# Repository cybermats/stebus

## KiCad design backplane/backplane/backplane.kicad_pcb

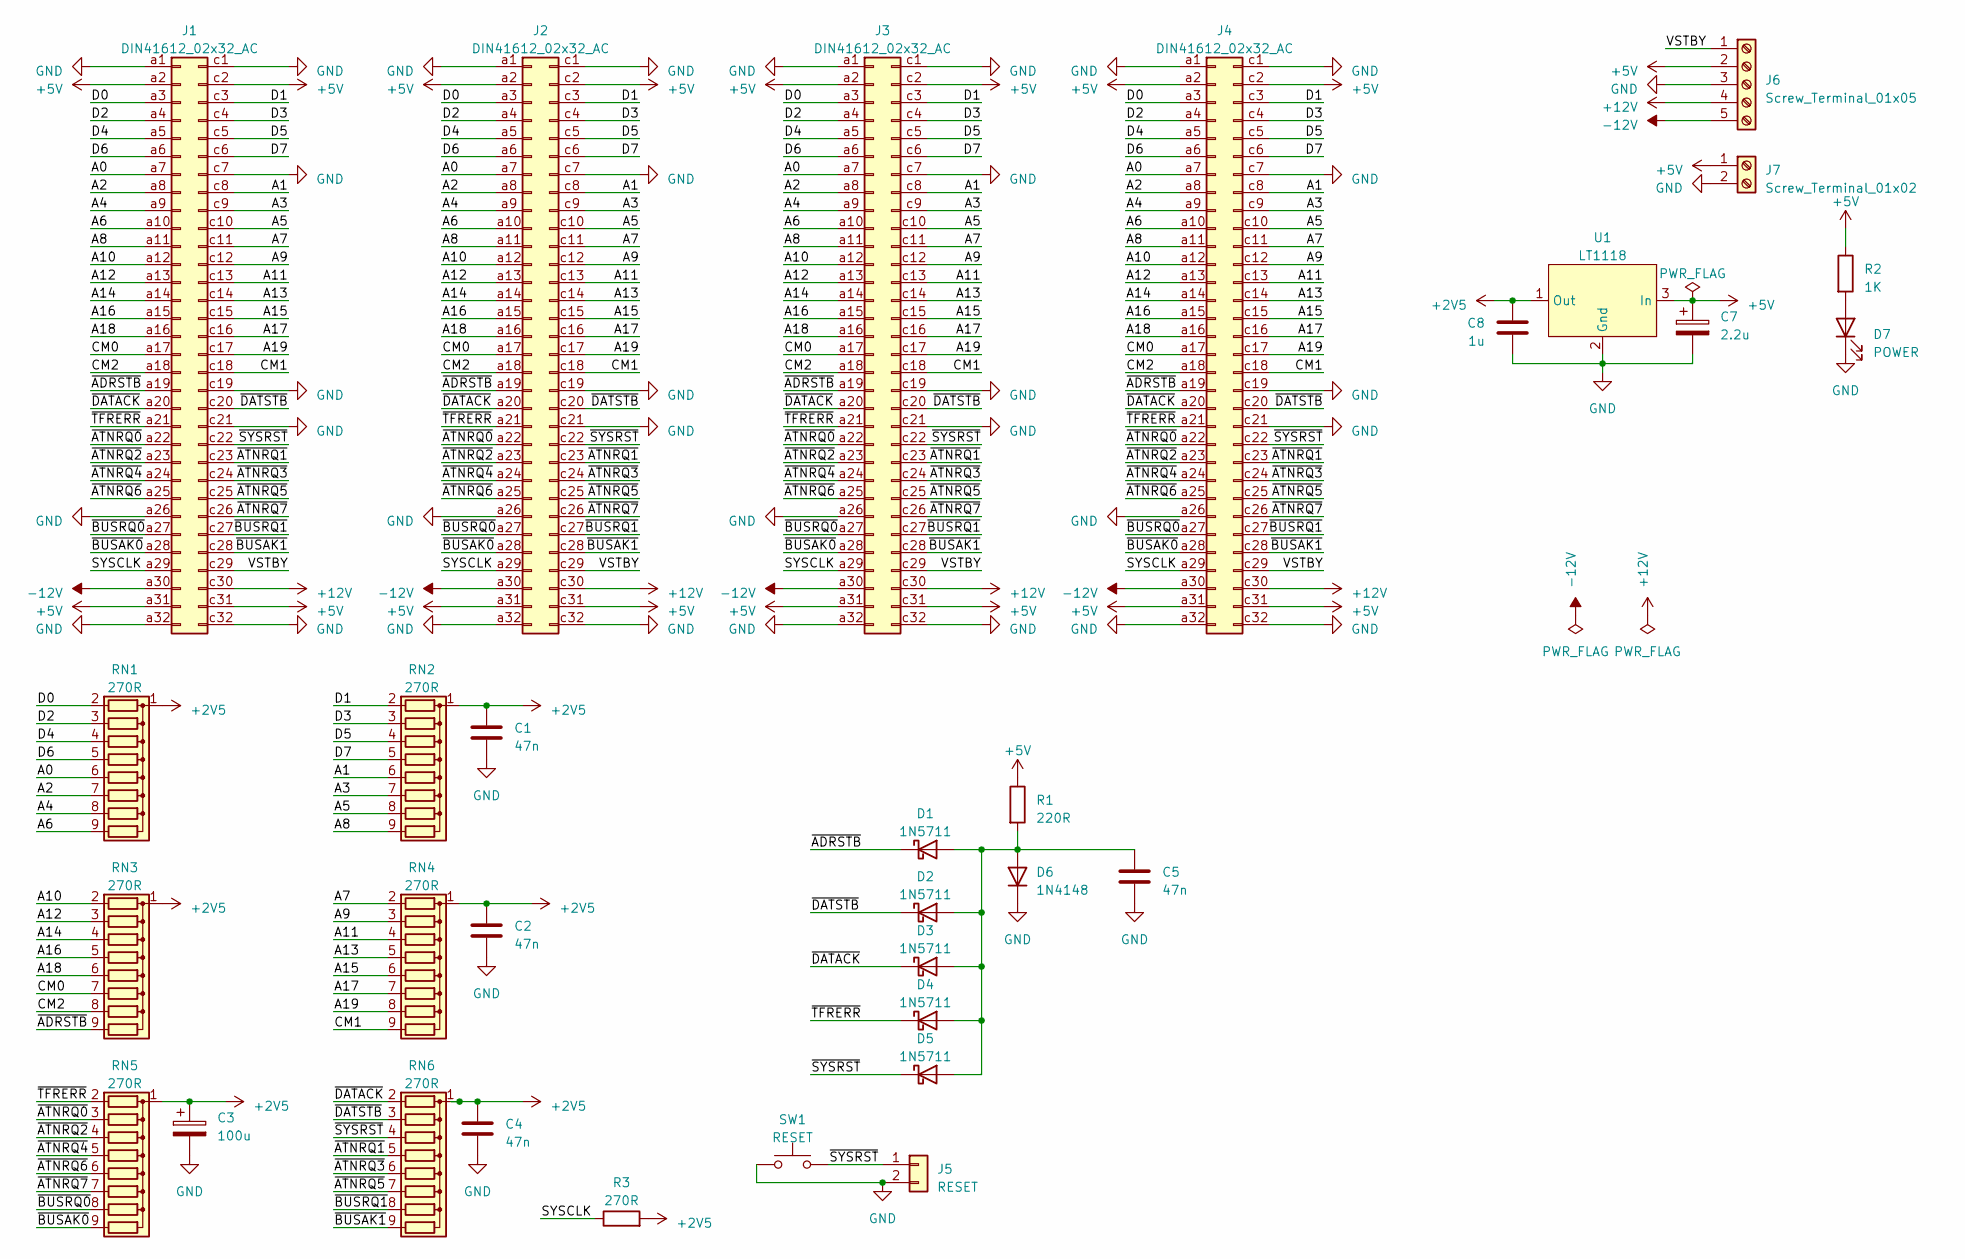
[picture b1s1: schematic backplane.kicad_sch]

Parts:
C1, C2, C4, C5: 47n; C_Disc_D6.0mm_W2.5mm_P5.00mm
C3: 100u; CP_Radial_D5.0mm_P2.00mm
C7: 2.2u; CP_Radial_D5.0mm_P2.00mm
C8: 1u; C_Disc_D6.0mm_W2.5mm_P5.00mm
D1, D2, D3, D4, D5: 1N5711; D_DO-35_SOD27_P7.62mm_Horizontal
D6: 1N4148; D_DO-35_SOD27_P7.62mm_Horizontal
D7: POWER; LED_D3.0mm_Clear
J1, J2, J3, J4: DIN41612_02x32_AC; DIN41612_C_2x32_Female_Vertical_THT
J5: RESET; PinHeader_1x02_P2.54mm_Vertical
J6: Screw_Terminal_01x05; PinHeader_1x05_P2.54mm_Vertical
J7: Screw_Terminal_01x02; TerminalBlock_Phoenix_MPT-0,5-2-2.54_1x02_P2.54mm_Horizontal
R1: 220R; R_Axial_DIN0207_L6.3mm_D2.5mm_P7.62mm_Horizontal
R2: 1K; R_Axial_DIN0207_L6.3mm_D2.5mm_P7.62mm_Horizontal
R3: 270R; R_Axial_DIN0207_L6.3mm_D2.5mm_P7.62mm_Horizontal
RN1, RN2, RN3, RN4, RN5, RN6: 270R; R_Array_SIP9
SW1: RESET; SW_PUSH_6mm
U1: LT1118; SOT-223-3_TabPin2

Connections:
+2V5: C1.1, C2.1, C3.1, C4.1, C8.1, R3.2, RN1.1 (common), RN2.1 (common), RN3.1 (common), RN4.1 (common), RN5.1 (common), RN6.1 (common), U1.1 (Out)
+5V: C7.1, J1.a2, J1.a31, J1.c2, J1.c31, J2.a2, J2.a31, J2.c2, J2.c31, J3.a2, J3.a31, J3.c2, J3.c31, J4.a2, J4.a31, J4.c2, J4.c31, J6.2, J7.1, R1.1, R2.1, U1.3 (In)
+12V: J1.c30, J2.c30, J3.c30, J4.c30, J6.4
-12V: J1.a30, J2.a30, J3.a30, J4.a30, J6.5
/A0: J1.a7, J2.a7, J3.a7, J4.a7, RN1.6 (R5)
/A1: J1.c8, J2.c8, J3.c8, J4.c8, RN2.6 (R5)
/A2: J1.a8, J2.a8, J3.a8, J4.a8, RN1.7 (R6)
/A3: J1.c9, J2.c9, J3.c9, J4.c9, RN2.7 (R6)
/A4: J1.a9, J2.a9, J3.a9, J4.a9, RN1.8 (R7)
/A5: J1.c10, J2.c10, J3.c10, J4.c10, RN2.8 (R7)
/A6: J1.a10, J2.a10, J3.a10, J4.a10, RN1.9 (R8)
/A7: J1.c11, J2.c11, J3.c11, J4.c11, RN4.2 (R1)
/A8: J1.a11, J2.a11, J3.a11, J4.a11, RN2.9 (R8)
/A9: J1.c12, J2.c12, J3.c12, J4.c12, RN4.3 (R2)
/A10: J1.a12, J2.a12, J3.a12, J4.a12, RN3.2 (R1)
/A11: J1.c13, J2.c13, J3.c13, J4.c13, RN4.4 (R3)
/A12: J1.a13, J2.a13, J3.a13, J4.a13, RN3.3 (R2)
/A13: J1.c14, J2.c14, J3.c14, J4.c14, RN4.5 (R4)
/A14: J1.a14, J2.a14, J3.a14, J4.a14, RN3.4 (R3)
/A15: J1.c15, J2.c15, J3.c15, J4.c15, RN4.6 (R5)
/A16: J1.a15, J2.a15, J3.a15, J4.a15, RN3.5 (R4)
/A17: J1.c16, J2.c16, J3.c16, J4.c16, RN4.7 (R6)
/A18: J1.a16, J2.a16, J3.a16, J4.a16, RN3.6 (R5)
/A19: J1.c17, J2.c17, J3.c17, J4.c17, RN4.8 (R7)
/CM0: J1.a17, J2.a17, J3.a17, J4.a17, RN3.7 (R6)
/CM1: J1.c18, J2.c18, J3.c18, J4.c18, RN4.9 (R8)
/CM2: J1.a18, J2.a18, J3.a18, J4.a18, RN3.8 (R7)
/D0: J1.a3, J2.a3, J3.a3, J4.a3, RN1.2 (R1)
/D1: J1.c3, J2.c3, J3.c3, J4.c3, RN2.2 (R1)
/D2: J1.a4, J2.a4, J3.a4, J4.a4, RN1.3 (R2)
/D3: J1.c4, J2.c4, J3.c4, J4.c4, RN2.3 (R2)
/D4: J1.a5, J2.a5, J3.a5, J4.a5, RN1.4 (R3)
/D5: J1.c5, J2.c5, J3.c5, J4.c5, RN2.4 (R3)
/D6: J1.a6, J2.a6, J3.a6, J4.a6, RN1.5 (R4)
/D7: J1.c6, J2.c6, J3.c6, J4.c6, RN2.5 (R4)
/SYSCLK: J1.a29, J2.a29, J3.a29, J4.a29, R3.1
/VSTBY: J1.c29, J2.c29, J3.c29, J4.c29, J6.1
/~ADRSTB: D1.1 (K), J1.a19, J2.a19, J3.a19, J4.a19, RN3.9 (R8)
/~ATNRQ0: J1.a22, J2.a22, J3.a22, J4.a22, RN5.3 (R2)
/~ATNRQ1: J1.c23, J2.c23, J3.c23, J4.c23, RN6.5 (R4)
/~ATNRQ2: J1.a23, J2.a23, J3.a23, J4.a23, RN5.4 (R3)
/~ATNRQ3: J1.c24, J2.c24, J3.c24, J4.c24, RN6.6 (R5)
/~ATNRQ4: J1.a24, J2.a24, J3.a24, J4.a24, RN5.5 (R4)
/~ATNRQ5: J1.c25, J2.c25, J3.c25, J4.c25, RN6.7 (R6)
/~ATNRQ6: J1.a25, J2.a25, J3.a25, J4.a25, RN5.6 (R5)
/~ATNRQ7: J1.c26, J2.c26, J3.c26, J4.c26, RN5.7 (R6)
/~BUSAK0: J1.a28, J2.a28, J3.a28, J4.a28, RN5.9 (R8)
/~BUSAK1: J1.c28, J2.c28, J3.c28, J4.c28, RN6.9 (R8)
/~BUSRQ0: J1.a27, J2.a27, J3.a27, J4.a27, RN5.8 (R7)
/~BUSRQ1: J1.c27, J2.c27, J3.c27, J4.c27, RN6.8 (R7)
/~DATACK: D3.1 (K), J1.a20, J2.a20, J3.a20, J4.a20, RN6.2 (R1)
/~DATSTB: D2.1 (K), J1.c20, J2.c20, J3.c20, J4.c20, RN6.3 (R2)
/~SYSRST: D5.1 (K), J1.c22, J2.c22, J3.c22, J4.c22, J5.1, RN6.4 (R3), SW1.2
/~TFRERR: D4.1 (K), J1.a21, J2.a21, J3.a21, J4.a21, RN5.2 (R1)
GND: C1.2, C2.2, C3.2, C4.2, C5.2, C7.2, C8.2, D6.1 (K), D7.1 (K), J1.a1, J1.a26, J1.a32, J1.c1, J1.c7, J1.c19, J1.c21, J1.c32, J2.a1, J2.a26, J2.a32, J2.c1, J2.c7, J2.c19, J2.c21, J2.c32, J3.a1, J3.a26, J3.a32, J3.c1, J3.c7, J3.c19, J3.c21, J3.c32, J4.a1, J4.a26, J4.a32, J4.c1, J4.c7, J4.c19, J4.c21, J4.c32, J5.2, J6.3, J7.2, SW1.1, U1.2 (Gnd)
unnamed: C5.1, D1.2 (A), D2.2 (A), D3.2 (A), D4.2 (A), D5.2 (A), D6.2 (A), R1.2
unnamed: D7.2 (A), R2.2

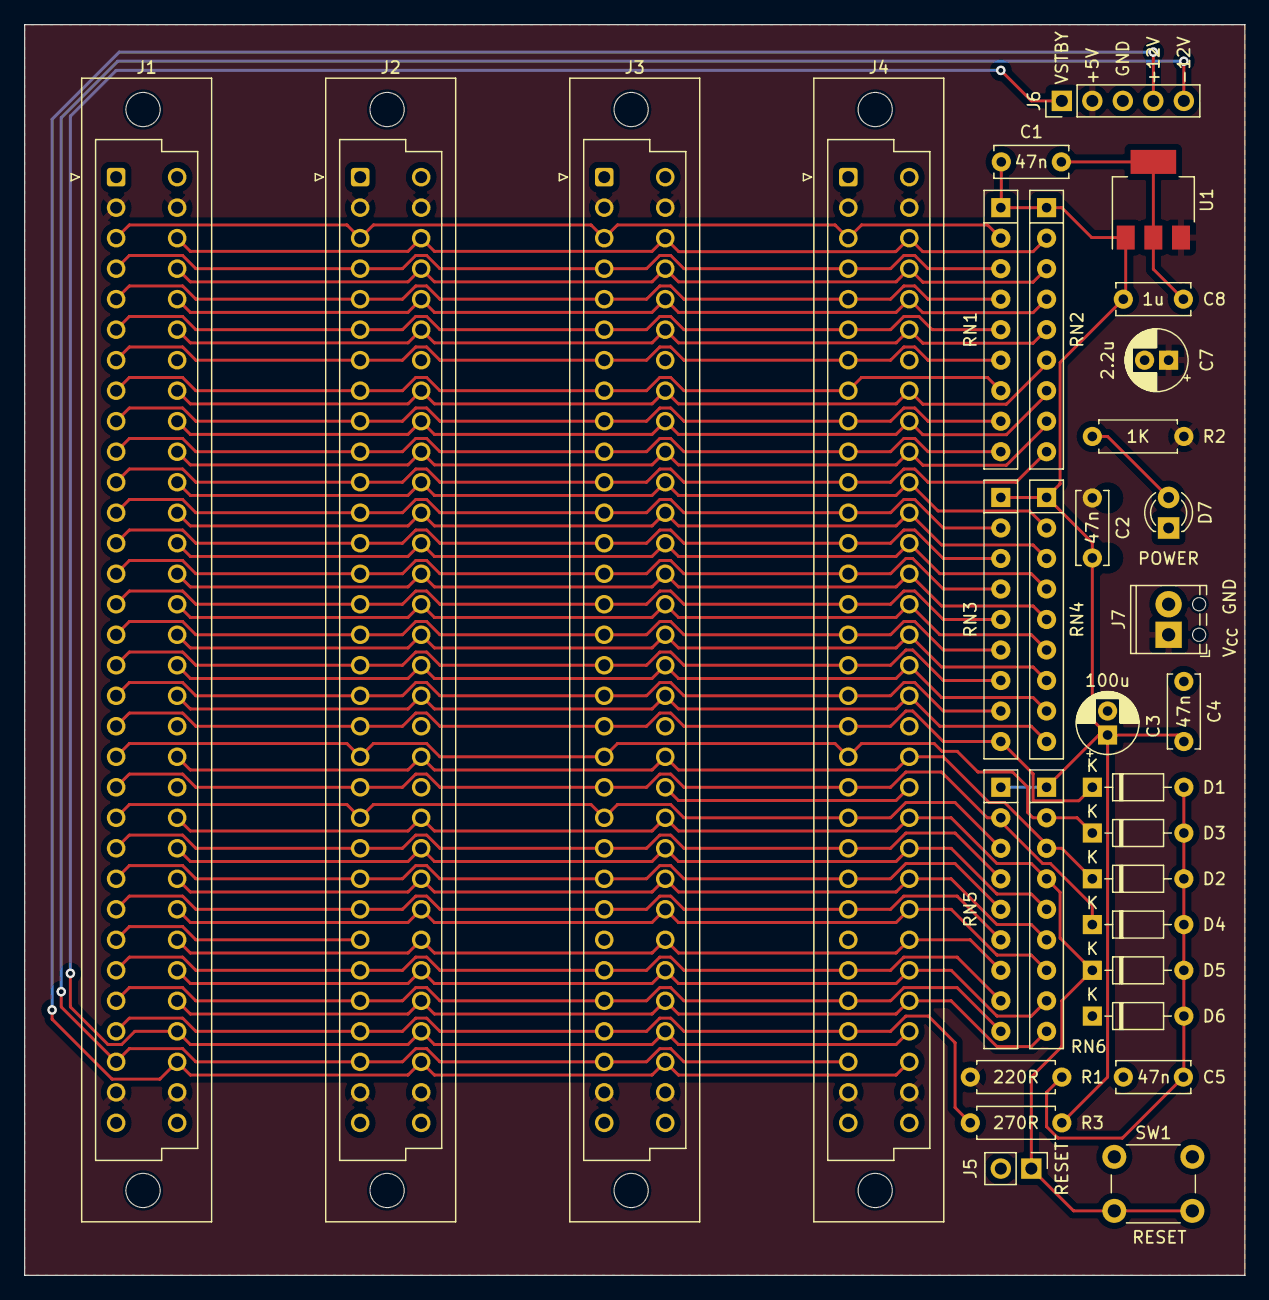
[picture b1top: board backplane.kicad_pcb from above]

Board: 2 copper layers, 101.6 x 104.1 mm, 32 parts (0 on the bottom side), 57 nets.

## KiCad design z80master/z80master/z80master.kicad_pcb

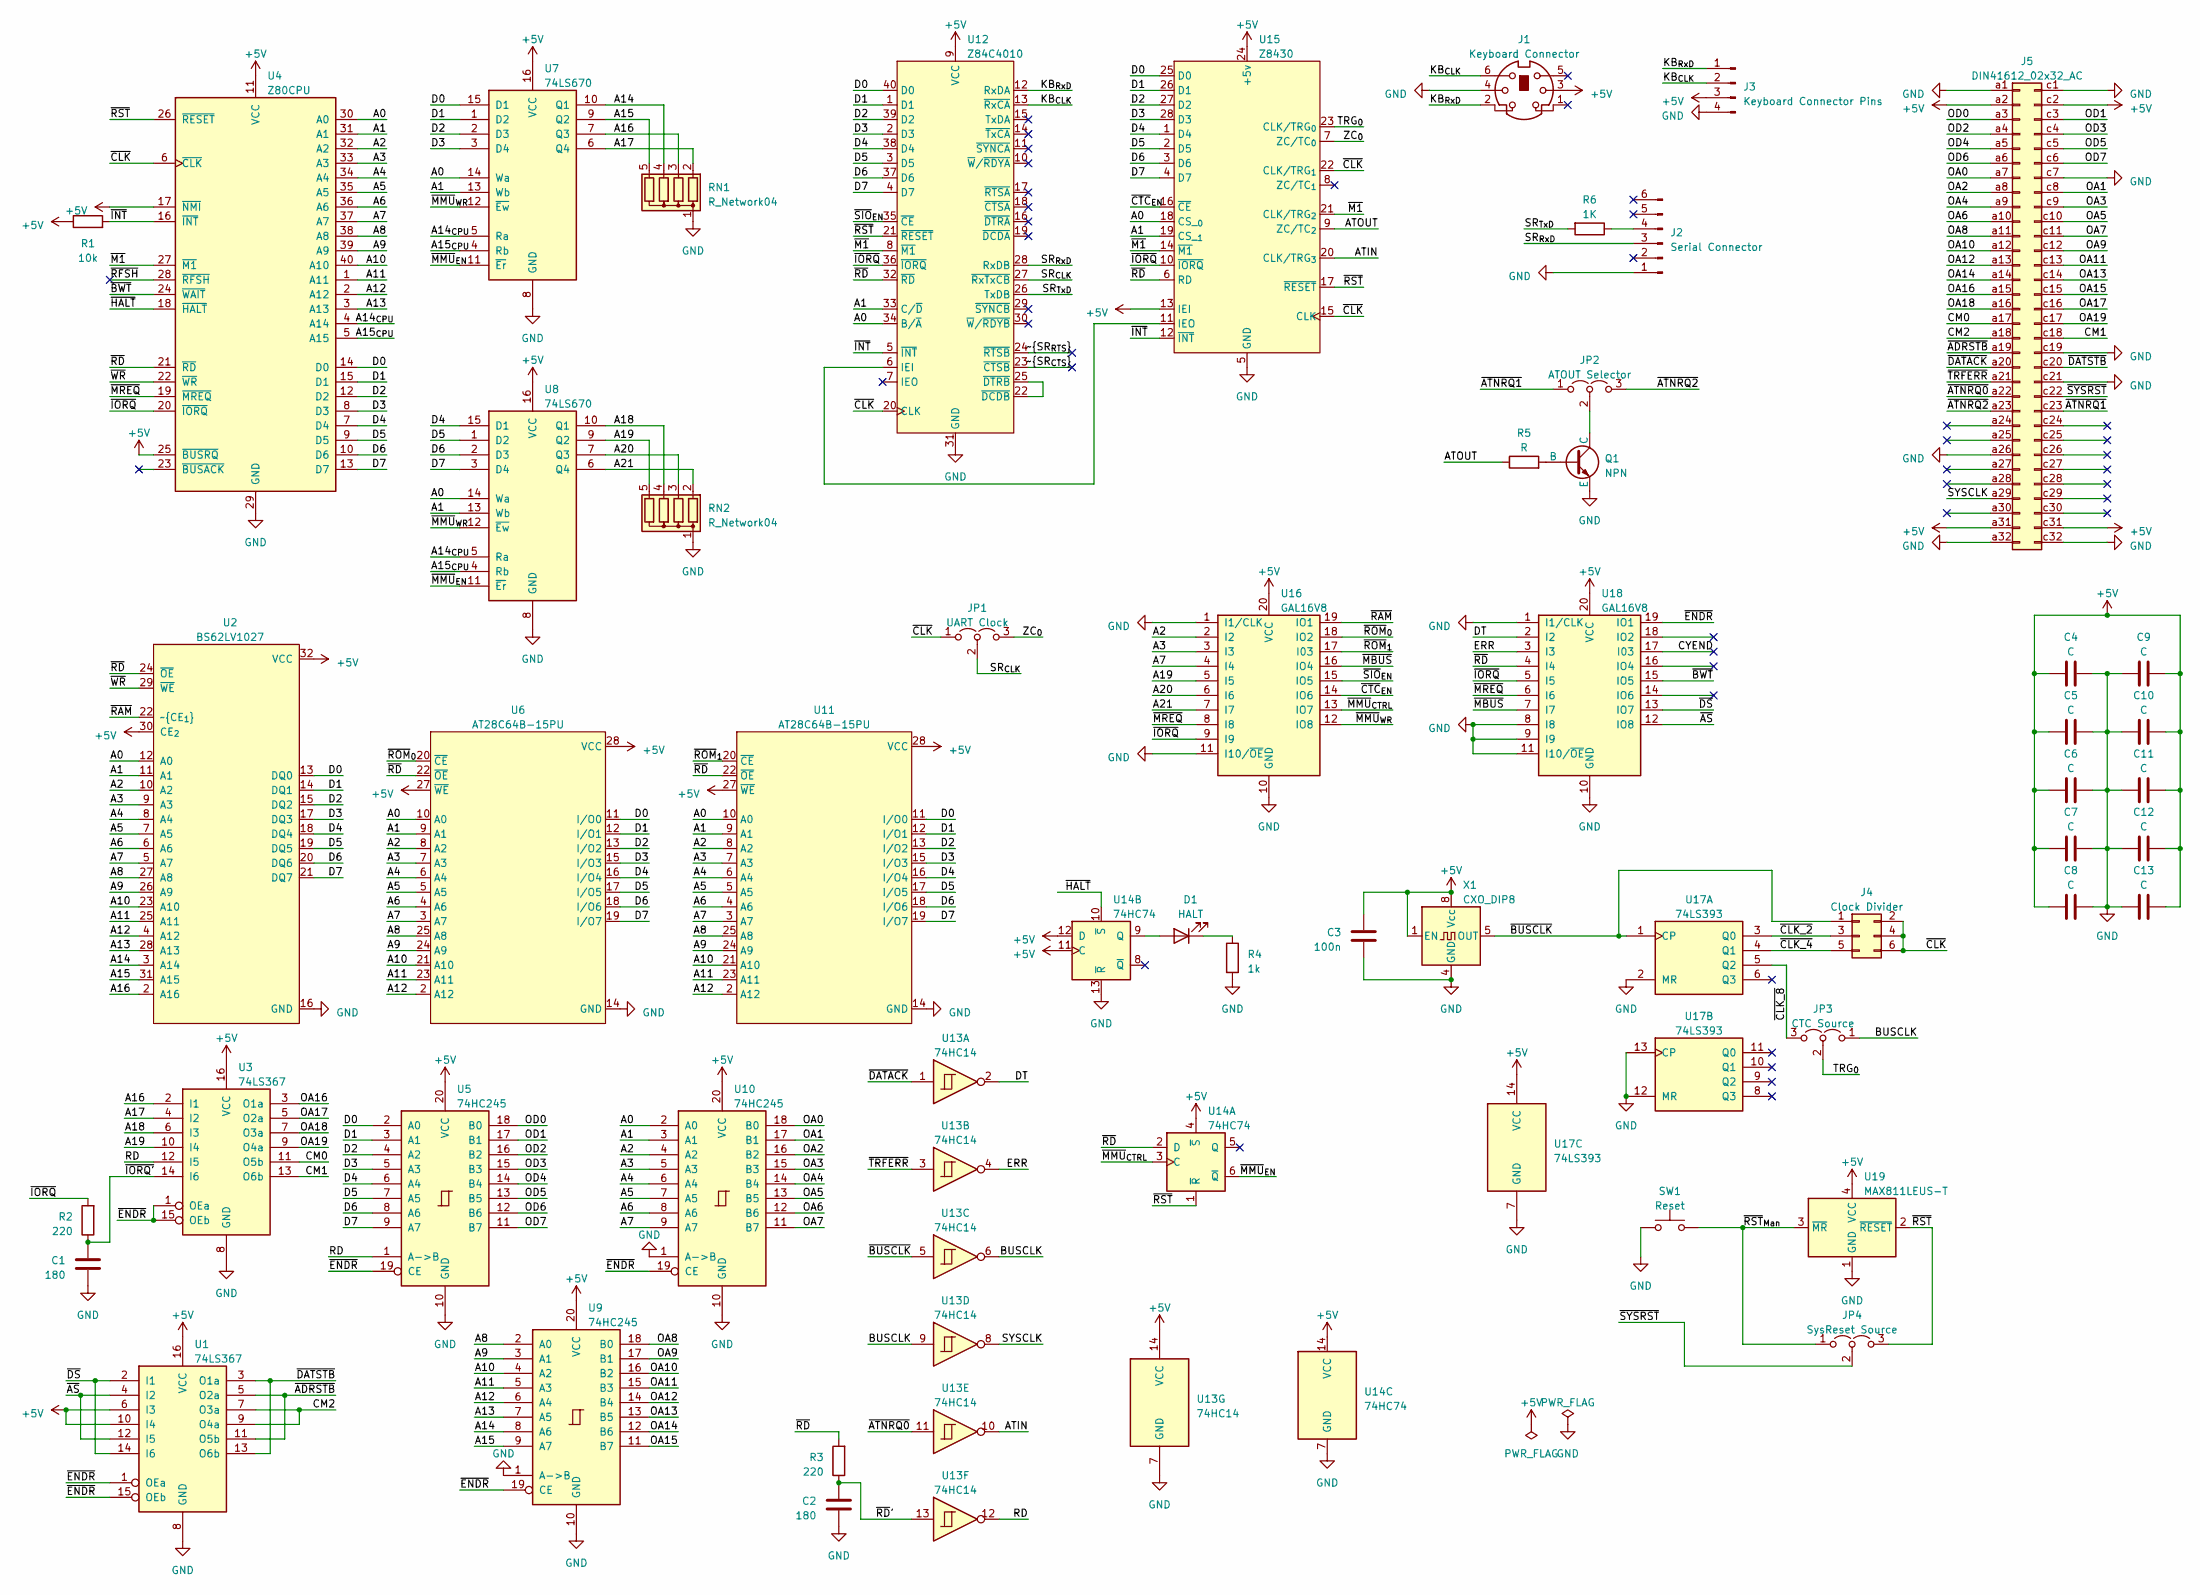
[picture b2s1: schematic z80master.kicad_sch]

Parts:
C1, C2: 180; C_Disc_D6.0mm_W2.5mm_P5.00mm
C3: 100n; C_Disc_D6.0mm_W2.5mm_P5.00mm
C4, C5, C6, C7, C8, C9, C10, C11, C12, C13: C; C_Disc_D6.0mm_W2.5mm_P5.00mm
D1: HALT; LED_D3.0mm_Clear
J1: Keyboard Connector; TM 0508 A6
J2: Serial Connector; PinHeader_1x06_P2.54mm_Vertical
J3: Keyboard Connector Pins; PinHeader_1x04_P2.54mm_Vertical
J4: Clock Divider; PinHeader_2x03_P2.54mm_Vertical
J5: DIN41612_02x32_AC; DIN41612_C_2x32_Male_Horizontal_THT
JP1: UART Clock; PinHeader_1x03_P2.54mm_Vertical
JP2: ATOUT Selector; PinHeader_1x03_P2.54mm_Vertical
JP3: CTC Source; PinHeader_1x03_P2.54mm_Vertical
JP4: SysReset Source; PinHeader_1x03_P2.54mm_Vertical
Q1: NPN; TO-92_HandSolder
R1: 10k; R_Axial_DIN0207_L6.3mm_D2.5mm_P7.62mm_Horizontal
R2, R3: 220; R_Axial_DIN0207_L6.3mm_D2.5mm_P7.62mm_Horizontal
R4: 1k; R_Axial_DIN0207_L6.3mm_D2.5mm_P7.62mm_Horizontal
R5: R; R_Axial_DIN0207_L6.3mm_D2.5mm_P7.62mm_Horizontal
R6: 1K; R_Axial_DIN0207_L6.3mm_D2.5mm_P7.62mm_Horizontal
RN1, RN2: R_Network04; R_Array_SIP5
SW1: Reset; SW_PUSH_6mm
U1, U3: 74LS367; DIP-16_W7.62mm_Socket
U2: BS62LV1027; DIP-32_W15.24mm
U4: Z80CPU; DIP-40_W15.24mm_Socket
U5, U9, U10: 74HC245; DIP-20_W7.62mm_Socket
U6, U11: AT28C64B-15PU; DIP-28_W15.24mm
U7, U8: 74LS670; DIP-16_W7.62mm_Socket
U12: Z84C4010; DIP-40_W15.24mm_Socket
U13: 74HC14; DIP-14_W7.62mm_Socket
U14: 74HC74; DIP-14_W7.62mm_Socket
U15: Z8430; DIP-28_W15.24mm_Socket
U16, U18: GAL16V8; DIP-20_W7.62mm_Socket
U17: 74LS393; DIP-14_W7.62mm_Socket
U19: MAX811LEUS-T; SOT-143
X1: CXO_DIP8; Oscillator_DIP-8

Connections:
+5V: C3.2, C4.2, C5.2, C6.2, C7.2, C8.2, C9.1, C10.1, C11.1, C12.1, C13.1, J1.3, J3.3, J5.a2, J5.a31, J5.c2, J5.c31, R1.1, U1.6 (I3), U1.10 (I4), U1.16 (VCC), U2.30 (CE_{2}), U2.32 (VCC), U3.16 (VCC), U4.11 (VCC), U4.17 (~NMI), U4.25 (~BUSRQ), U5.20 (VCC), U6.27 (~WE), U6.28 (VCC), U7.16 (VCC), U8.16 (VCC), U9.20 (VCC), U10.20 (VCC), U11.27 (~WE), U11.28 (VCC), U12.9 (VCC), U13.14 (VCC), U14.4 (~S), U14.11 (C), U14.12 (D), U14.14 (VCC), U15.13 (IEI), U15.24 (+5v), U16.20 (VCC), U17.14 (VCC), U18.20 (VCC), U19.4 (VCC), X1.1 (EN), X1.8 (Vcc)
/A0: U2.12 (A0), U4.30 (A0), U6.10 (A0), U7.14 (Wa), U8.14 (Wa), U10.2 (A0), U11.10 (A0), U12.34 (B/~A), U15.18 (CS__{0})
/A1: U2.11 (A1), U4.31 (A1), U6.9 (A1), U7.13 (Wb), U8.13 (Wb), U10.3 (A1), U11.9 (A1), U12.33 (C/~D), U15.19 (CS__{1})
/A2: U2.10 (A2), U4.32 (A2), U6.8 (A2), U10.4 (A2), U11.8 (A2), U16.2 (I2)
/A3: U2.9 (A3), U4.33 (A3), U6.7 (A3), U10.5 (A3), U11.7 (A3), U16.3 (I3)
/A4: U2.8 (A4), U4.34 (A4), U6.6 (A4), U10.6 (A4), U11.6 (A4)
/A5: U2.7 (A5), U4.35 (A5), U6.5 (A5), U10.7 (A5), U11.5 (A5)
/A6: U2.6 (A6), U4.36 (A6), U6.4 (A6), U10.8 (A6), U11.4 (A6)
/A7: U2.5 (A7), U4.37 (A7), U6.3 (A7), U10.9 (A7), U11.3 (A7), U16.4 (I4)
/A8: U2.27 (A8), U4.38 (A8), U6.25 (A8), U9.2 (A0), U11.25 (A8)
/A9: U2.26 (A9), U4.39 (A9), U6.24 (A9), U9.3 (A1), U11.24 (A9)
/A10: U2.23 (A10), U4.40 (A10), U6.21 (A10), U9.4 (A2), U11.21 (A10)
/A11: U2.25 (A11), U4.1 (A11), U6.23 (A11), U9.5 (A3), U11.23 (A11)
/A12: U2.4 (A12), U4.2 (A12), U6.2 (A12), U9.6 (A4), U11.2 (A12)
/A13: U2.28 (A13), U4.3 (A13), U9.7 (A5)
/A14: RN1.4 (R3), U2.3 (A14), U7.10 (Q1), U9.8 (A6)
/A14_{CPU}: U4.4 (A14), U7.5 (Ra), U8.5 (Ra)
/A15: RN1.5 (R4), U2.31 (A15), U7.9 (Q2), U9.9 (A7)
/A15_{CPU}: U4.5 (A15), U7.4 (Rb), U8.4 (Rb)
/A16: RN1.3 (R2), U2.2 (A16), U3.2 (I1), U7.7 (Q3)
/A17: RN1.2 (R1), U3.4 (I2), U7.6 (Q4)
/A18: RN2.4 (R3), U3.6 (I3), U8.10 (Q1)
/A19: RN2.5 (R4), U3.10 (I4), U8.9 (Q2), U16.5 (I5)
/A20: RN2.3 (R2), U8.7 (Q3), U16.6 (I6)
/A21: RN2.2 (R1), U8.6 (Q4), U16.7 (I7)
/ATIN: U13.10, U15.20 (CLK/TRG_{3})
/ATOUT: R5.1, U15.9 (ZC/TC_{2})
/BUSCLK: JP3.1 (A), U13.6, U13.9
/CM0: J5.a17, U3.11 (O5b)
/CM1: J5.c18, U3.13 (O6b)
/CM2: J5.a18, U1.7 (O3a), U1.9 (O4a)
/CYEND: U18.17 (I03)
/D0: U2.13 (DQ0), U4.14 (D0), U5.2 (A0), U6.11 (I/O0), U7.15 (D1), U11.11 (I/O0), U12.40 (D0), U15.25 (D0)
/D1: U2.14 (DQ1), U4.15 (D1), U5.3 (A1), U6.12 (I/O1), U7.1 (D2), U11.12 (I/O1), U12.1 (D1), U15.26 (D1)
/D2: U2.15 (DQ2), U4.12 (D2), U5.4 (A2), U6.13 (I/O2), U7.2 (D3), U11.13 (I/O2), U12.39 (D2), U15.27 (D2)
/D3: U2.17 (DQ3), U4.8 (D3), U5.5 (A3), U6.15 (I/O3), U7.3 (D4), U11.15 (I/O3), U12.2 (D3), U15.28 (D3)
/D4: U2.18 (DQ4), U4.7 (D4), U5.6 (A4), U6.16 (I/O4), U8.15 (D1), U11.16 (I/O4), U12.38 (D4), U15.1 (D4)
/D5: U2.19 (DQ5), U4.9 (D5), U5.7 (A5), U6.17 (I/O5), U8.1 (D2), U11.17 (I/O5), U12.3 (D5), U15.2 (D5)
/D6: U2.20 (DQ6), U4.10 (D6), U5.8 (A6), U6.18 (I/O6), U8.2 (D3), U11.18 (I/O6), U12.37 (D6), U15.3 (D6)
/D7: U2.21 (DQ7), U4.13 (D7), U5.9 (A7), U6.19 (I/O7), U8.3 (D4), U11.19 (I/O7), U12.4 (D7), U15.4 (D7)
/DT: U13.2, U18.2 (I2)
/ERR: U13.4, U18.3 (I3)
/KB_{CLK}: J1.6, J3.2, U12.13 (~RxCA)
/KB_{RxD}: J1.2, J3.1, U12.12 (RxDA)
/OA0: J5.a7, U10.18 (B0)
/OA1: J5.c8, U10.17 (B1)
/OA2: J5.a8, U10.16 (B2)
/OA3: J5.c9, U10.15 (B3)
/OA4: J5.a9, U10.14 (B4)
/OA5: J5.c10, U10.13 (B5)
/OA6: J5.a10, U10.12 (B6)
/OA7: J5.c11, U10.11 (B7)
/OA8: J5.a11, U9.18 (B0)
/OA9: J5.c12, U9.17 (B1)
/OA10: J5.a12, U9.16 (B2)
/OA11: J5.c13, U9.15 (B3)
/OA12: J5.a13, U9.14 (B4)
/OA13: J5.c14, U9.13 (B5)
/OA14: J5.a14, U9.12 (B6)
/OA15: J5.c15, U9.11 (B7)
/OA16: J5.a15, U3.3 (O1a)
/OA17: J5.c16, U3.5 (O2a)
/OA18: J5.a16, U3.7 (O3a)
/OA19: J5.c17, U3.9 (O4a)
/OD0: J5.a3, U5.18 (B0)
/OD1: J5.c3, U5.17 (B1)
/OD2: J5.a4, U5.16 (B2)
/OD3: J5.c4, U5.15 (B3)
/OD4: J5.a5, U5.14 (B4)
/OD5: J5.c5, U5.13 (B5)
/OD6: J5.a6, U5.12 (B6)
/OD7: J5.c6, U5.11 (B7)
/RD: U3.12 (I5), U5.1 (A->B), U13.12
/SR_{CLK}: JP1.2 (C), U12.27 (~RxTxCB)
/SR_{RxD}: J2.3, U12.28 (RxDB)
/SR_{TxD}: R6.2, U12.26 (TxDB)
/SYSCLK: J5.a29, U13.8
/TRG_{0}: JP3.2 (C), U15.23 (CLK/TRG_{0})
/ZC_{0}: JP1.3 (B), U15.7 (ZC/TC_{0})
/~ADRSTB: J5.a19, U1.5 (O2a), U1.11 (O5b)
/~AS: U1.4 (I2), U1.12 (I5), U18.12 (IO8)
/~ATNRQ0: J5.a22, U13.11
/~ATNRQ1: J5.c23, JP2.1 (A)
/~ATNRQ2: J5.a23, JP2.3 (B)
/~BUSCLK: J4.1, U13.5, U17.1 (CP), X1.5 (OUT)
/~BWT: U4.24 (~WAIT), U18.15 (IO5)
/~CLK_2: J4.3, U17.3 (Q0)
/~CLK_4: J4.5, U17.4 (Q1)
/~CLK_8: JP3.3 (B), U17.5 (Q2)
/~CLK: J4.2, J4.4, J4.6, JP1.1 (A), U4.6 (~CLK), U12.20 (CLK), U15.15 (CLK), U15.22 (CLK/TRG_{1})
/~CTC_{EN}: U15.16 (~CE), U16.14 (IO6)
/~DATACK: J5.a20, U13.1
/~DATSTB: J5.c20, U1.3 (O1a), U1.13 (O6b)
/~DS: U1.2 (I1), U1.14 (I6), U18.13 (IO7)
/~ENDR: U1.1 (OEa), U1.15 (OEb), U3.1 (OEa), U3.15 (OEb), U5.19 (CE), U9.19 (CE), U10.19 (CE), U18.19 (IO1)
/~HALT: U4.18 (~HALT), U14.10 (~S)
/~INT: R1.2, U4.16 (~INT), U12.5 (~INT), U15.12 (~INT)
/~IORQ': C1.1, R2.1, U3.14 (I6)
/~IORQ: R2.2, U4.20 (~IORQ), U12.36 (~IORQ), U15.10 (~IORQ), U16.9 (I9), U18.5 (I5)
/~M1: U4.27 (~M1), U12.8 (~M1), U15.14 (~M1), U15.21 (CLK/TRG_{2})
/~MBUS: U16.16 (IO4), U18.7 (I7)
/~MMU_{CTRL}: U14.3 (C), U16.13 (IO7)
/~MMU_{EN}: U7.11 (~Er), U8.11 (~Er), U14.6 (~Q)
/~MMU_{WR}: U7.12 (~Ew), U8.12 (~Ew), U16.12 (IO8)
/~MREQ: U4.19 (~MREQ), U16.8 (I8), U18.6 (I6)
/~RAM: U2.22 (~CE_{1}), U16.19 (IO1)
/~RD: R3.2, U2.24 (~OE), U4.21 (~RD), U6.22 (~OE), U11.22 (~OE), U12.32 (~RD), U14.2 (D), U15.6 (RD), U18.4 (I4)
/~RD': C2.1, R3.1, U13.13
/~RFSH: U4.28 (~RFSH)
/~ROM_{0}: U6.20 (~CE), U16.18 (IO2)
/~ROM_{1}: U11.20 (~CE), U16.17 (I03)
/~RST: JP4.3 (B), U4.26 (~RESET), U12.21 (~RESET), U14.1 (~R), U15.17 (~RESET), U19.2 (~RESET)
/~RST_{Man}: JP4.1 (A), SW1.2, U19.3 (~MR)
/~SIO_{EN}: U12.35 (~CE), U16.15 (IO5)
/~SR_{CTS}: U12.23 (~CTSB)
/~SR_{RTS}: U12.24 (~RTSB)
/~SYSRST: J5.c22, JP4.2 (C)
/~TRFERR: J5.a21, U13.3
/~WR: U2.29 (~WE), U4.22 (~WR)
GND: C1.2, C2.2, C3.1, C4.1, C5.1, C6.1, C7.1, C8.1, C9.2, C10.2, C11.2, C12.2, C13.2, J1.4, J2.1, J3.4, J5.a1, J5.a26, J5.a32, J5.c1, J5.c7, J5.c19, J5.c21, J5.c32, Q1.3 (E), R4.2, RN1.1 (common), RN2.1 (common), SW1.1, U1.8 (GND), U2.16 (GND), U3.8 (GND), U4.29 (GND), U5.10 (GND), U6.14 (GND), U7.8 (GND), U8.8 (GND), U9.1 (A->B), U9.10 (GND), U10.1 (A->B), U10.10 (GND), U11.14 (GND), U12.31 (GND), U13.7 (GND), U14.7 (GND), U14.13 (~R), U15.5 (GND), U16.1 (I1/CLK), U16.10 (GND), U16.11 (I10/~OE), U17.2 (MR), U17.7 (GND), U17.12 (MR), U17.13 (CP), U18.1 (I1/CLK), U18.8 (I8), U18.9 (I9), U18.10 (GND), U18.11 (I10/~OE), U19.1 (GND), X1.4 (GND)
unnamed: D1.2 (A), U14.9 (Q)
unnamed: D1.1 (K), R4.1
unnamed: J2.4, R6.1
unnamed: JP2.2 (C), Q1.1 (C)
unnamed: Q1.2 (B), R5.2
unnamed: U12.6 (IEI), U15.11 (IEO)
unnamed: U12.22 (~DCDB), U12.25 (~DTRB)

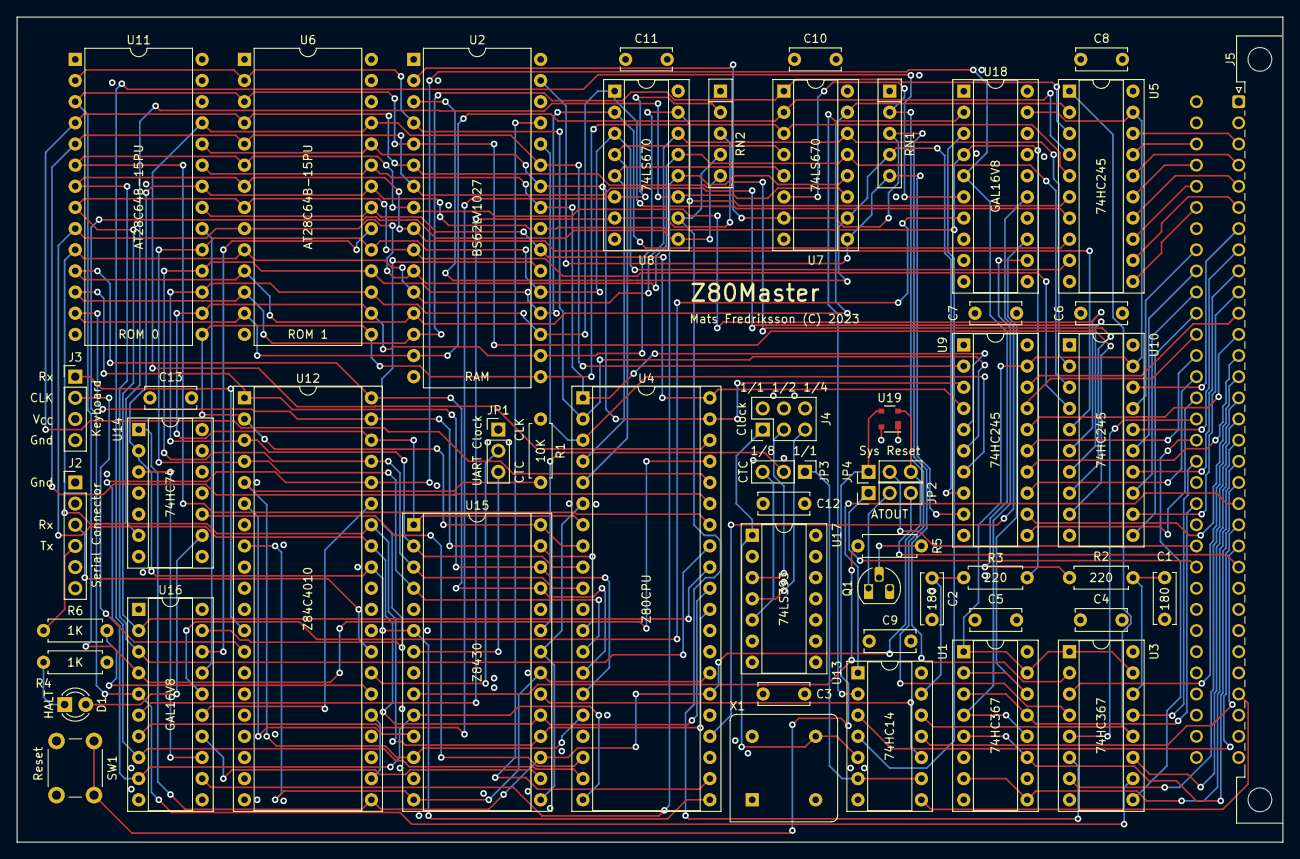
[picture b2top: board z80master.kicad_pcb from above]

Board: 4 copper layers, 152.0 x 99.1 mm, 52 parts (0 on the bottom side), 123 nets.

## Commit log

2023-06-09 main parts
2023-06-09 Adding wincupl files
2023-06-09 Adding readme and better document the PLD
2023-06-09 Adding licence.
2023-06-09 Rename wincupl directory
2023-06-09 Adding STEBus CPLD controller
2023-06-09 First simulation of STEBus Controller
2023-06-09 Fixing STEBus controller and adding tests.
2023-06-17 Added counter. Connected everything
2023-06-17 Assigned symbols
2023-06-18 laying out the board
2023-06-18 Adding data bus
2023-06-25 Rearranging the PCB. Removed all traces.
2023-06-28 adding traces for clocks and addresses
2023-06-28 Increasing clearance for Clock lines
2023-07-07 Fully routed
2023-07-07 Fixed warnings from Aisler
2023-07-08 tidying up
2023-07-08 Adding labels
2023-07-30 adding backplane
2023-07-30 last minute clean up
2023-07-30 General clean up of backplane
2023-07-30 adding copper fills for top and bottom layers

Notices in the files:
z80master/z80master/z80master.kicad_pcb:
Mats Fredriksson (C) 2023
